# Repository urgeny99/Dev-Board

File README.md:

# This is a self made dev board that i can use on many different projects. For example mount it on a bread board and connect a small screen or something like that.
# Story
I made started this project without knowing almost anything about PCBs but with the time as i followed the tutrial more and more things got clear. I was not sure what to use this for but i started watching videos and and did research. It is actually a very cool project. I am not sure if it will be easy soldering at home but i like a challange so i'll try it.
I will probably be using this dev board with bread boards to try experimenting and i maybe order some more cool components to try out how they work. (e.g OLED screens, small sensors etc.)
## Parts
What this board has are:
- USB-C conmector
- 16Mb flash storage
- RP2040 "CPU"
- 12MHz Crystal Osillator
- Temperature sensor
- Small NeoPixel
- 20+ GPIO pins

## Based on @KaiTheJollyGuy’s tutorial on how to make a devboard

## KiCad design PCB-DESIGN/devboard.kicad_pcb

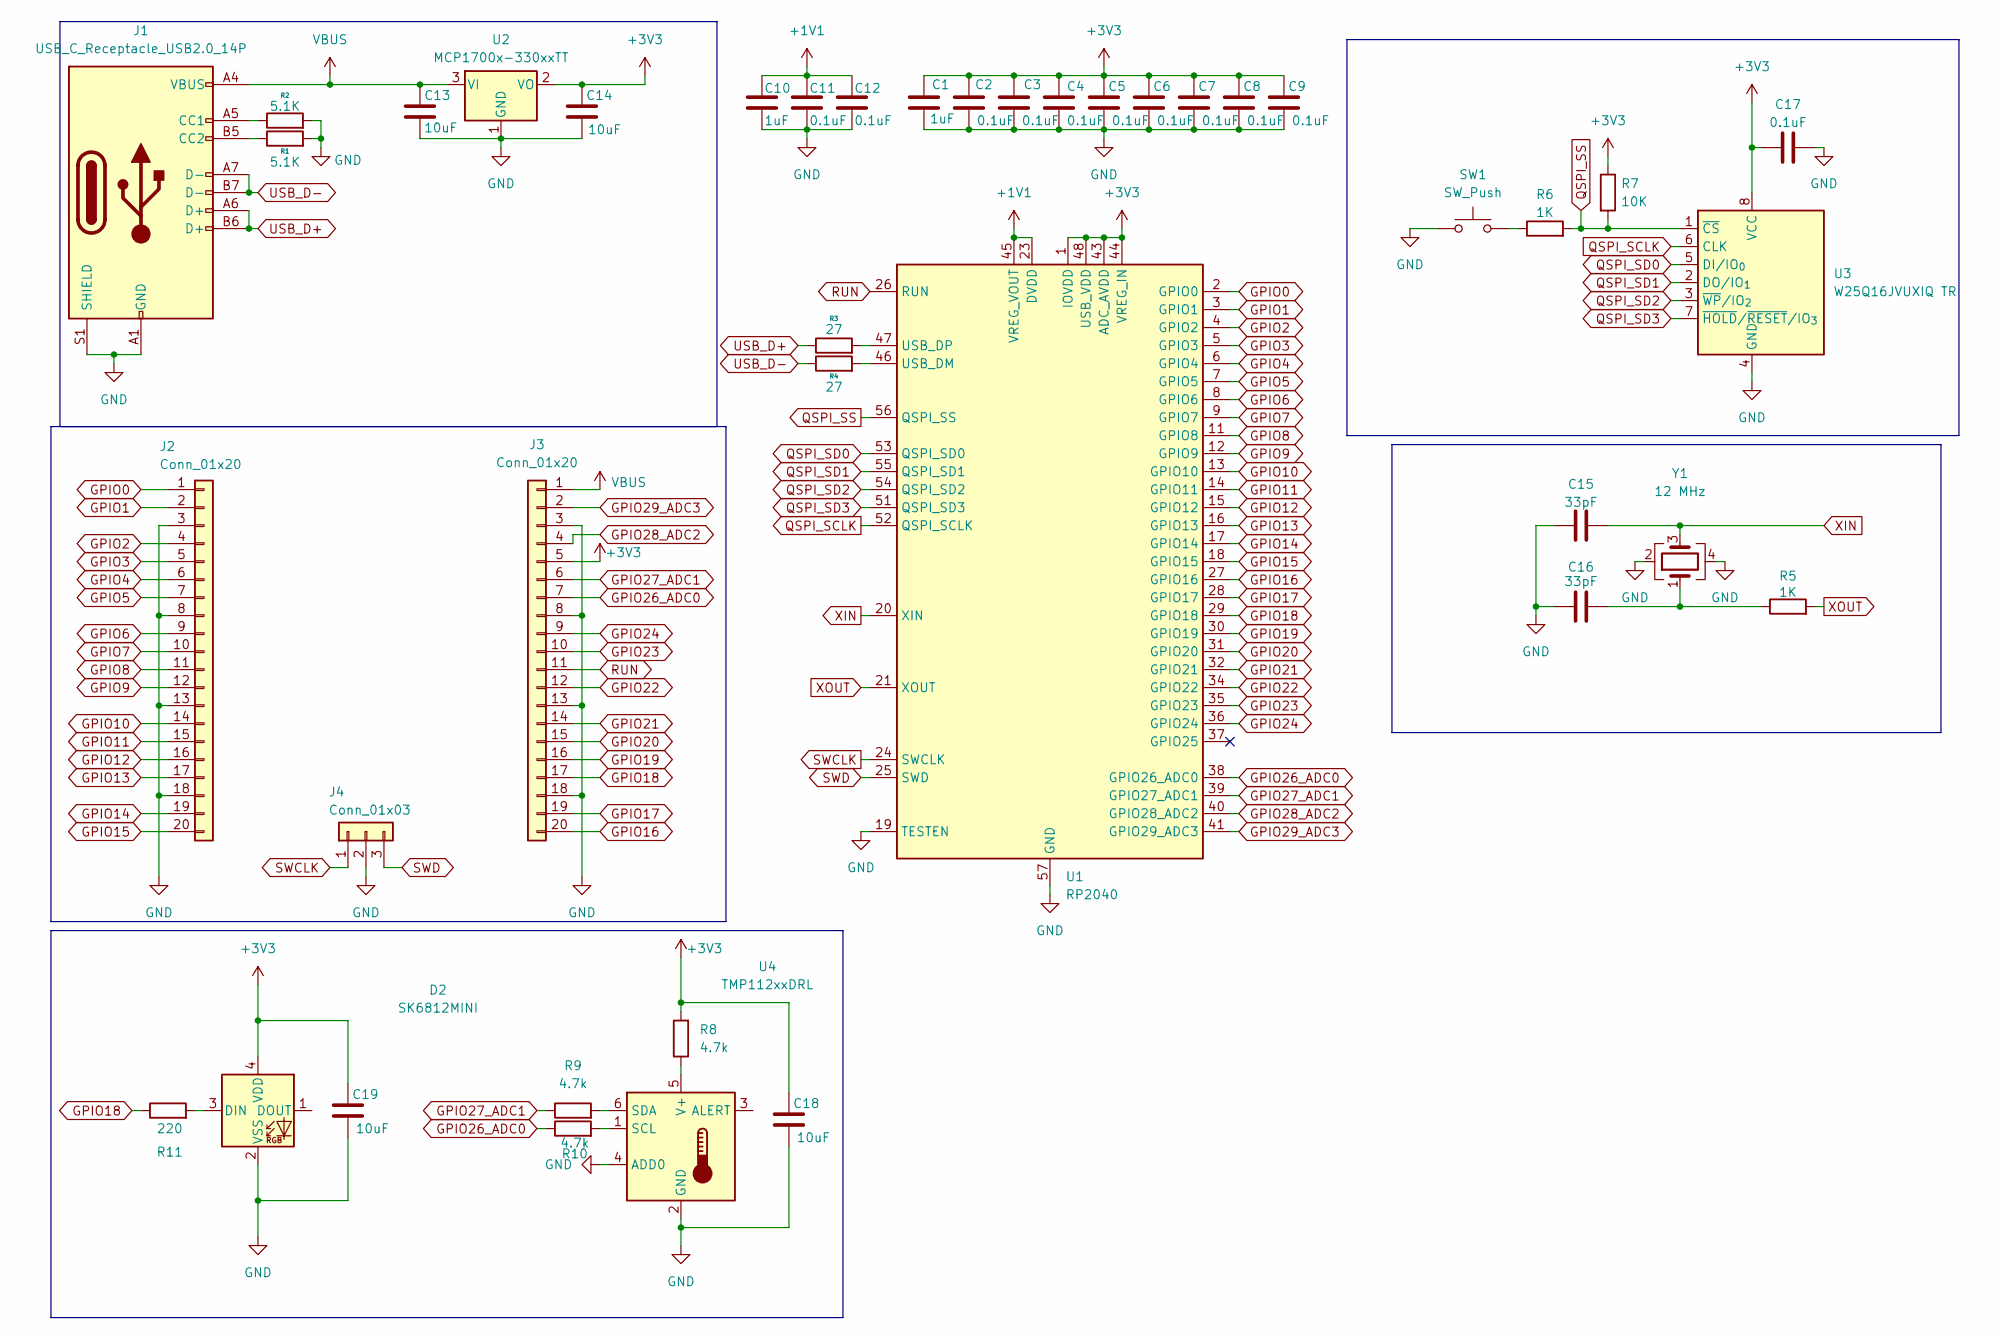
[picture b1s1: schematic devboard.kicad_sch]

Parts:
C1, C10: 1uF; C_0603_1608Metric
C2, C3, C4, C5, C6, C7, C8, C9, C11, C12, C17: 0.1uF; C_0603_1608Metric
C13, C14: 10uF; C_0805_2012Metric
C15, C16: 33pF; C_0603_1608Metric
C18, C19: 10uF; C_0603_1608Metric
D2: SK6812MINI; LED_SK6812MINI_PLCC4_3.5x3.5mm_P1.75mm
J1: USB_C_Receptacle_USB2.0_14P; USB_C_Receptacle_HRO_TYPE-C-31-M-12
J2, J3: Conn_01x20; PinHeader_1x20_P2.54mm_Vertical
J4: Conn_01x03; PinHeader_1x03_P2.54mm_Vertical
R1, R2: 5.1K; R_0603_1608Metric
R3, R4: 27; R_0603_1608Metric
R5, R6: 1K; R_0603_1608Metric
R7: 10K; R_0603_1608Metric
R8, R9, R10: 4.7k; R_0603_1608Metric
R11: 220; R_0603_1608Metric
SW1: SW_Push; SW_Push_SPST_NO_Alps_SKRK
U1: RP2040; QFN-56-1EP_7x7mm_P0.4mm_EP3.2x3.2mm
U2: MCP1700x-330xxTT; SOT-23
U3: W25Q16JVUXIQ TR; Winbond_USON-8-1EP_3x2mm_P0.5mm_EP0.2x1.6mm
U4: TMP112xxDRL; SOT-563
Y1: 12 MHz; Crystal_SMD_3225-4Pin_3.2x2.5mm

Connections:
+1V1: C10.1, C11.1, C12.1, U1.23 (DVDD), U1.45 (VREG_VOUT), U1.50 (DVDD)
+3V3: C1.1, C2.1, C3.1, C4.1, C5.1, C6.1, C7.1, C8.1, C9.1, C14.1, C17.1, C18.1, C19.1, D2.4 (VDD), J3.5, R7.1, R8.2, U1.1 (IOVDD), U1.10 (IOVDD), U1.22 (IOVDD), U1.33 (IOVDD), U1.42 (IOVDD), U1.43 (ADC_AVDD), U1.44 (VREG_IN), U1.48 (USB_VDD), U1.49 (IOVDD), U2.2 (VO), U3.8 (VCC)
GND: C1.2, C2.2, C3.2, C4.2, C5.2, C6.2, C7.2, C8.2, C9.2, C10.2, C11.2, C12.2, C13.2, C14.2, C15.1, C16.1, C17.2, C18.2, C19.2, D2.2 (VSS), J1.A1 (GND), J1.A12 (GND), J1.B1 (GND), J1.B12 (GND), J1.S1 (SHIELD), J2.3, J2.8, J2.13, J2.18, J3.3, J3.8, J3.13, J3.18, J4.2, R1.2, R2.2, SW1.1, U1.19 (TESTEN), U1.57 (GND), U2.1 (GND), U3.4 (GND), U4.2 (GND), U4.4 (ADD0), Y1.2, Y1.4
GPIO0: J2.1, U1.2 (GPIO0)
GPIO1: J2.2, U1.3 (GPIO1)
GPIO2: J2.4, U1.4 (GPIO2)
GPIO3: J2.5, U1.5 (GPIO3)
GPIO4: J2.6, U1.6 (GPIO4)
GPIO5: J2.7, U1.7 (GPIO5)
GPIO6: J2.9, U1.8 (GPIO6)
GPIO7: J2.10, U1.9 (GPIO7)
GPIO8: J2.11, U1.11 (GPIO8)
GPIO9: J2.12, U1.12 (GPIO9)
GPIO10: J2.14, U1.13 (GPIO10)
GPIO11: J2.15, U1.14 (GPIO11)
GPIO12: J2.16, U1.15 (GPIO12)
GPIO13: J2.17, U1.16 (GPIO13)
GPIO14: J2.19, U1.17 (GPIO14)
GPIO15: J2.20, U1.18 (GPIO15)
GPIO16: J3.20, U1.27 (GPIO16)
GPIO17: J3.19, U1.28 (GPIO17)
GPIO18: J3.17, R11.1, U1.29 (GPIO18)
GPIO19: J3.16, U1.30 (GPIO19)
GPIO20: J3.15, U1.31 (GPIO20)
GPIO21: J3.14, U1.32 (GPIO21)
GPIO22: J3.12, U1.34 (GPIO22)
GPIO23: J3.10, U1.35 (GPIO23)
GPIO24: J3.9, U1.36 (GPIO24)
GPIO26_ADC0: J3.7, R10.1, U1.38 (GPIO26_ADC0)
GPIO27_ADC1: J3.6, R9.1, U1.39 (GPIO27_ADC1)
GPIO28_ADC2: J3.4, U1.40 (GPIO28_ADC2)
GPIO29_ADC3: J3.2, U1.41 (GPIO29_ADC3)
unnamed: C16.2, R5.1, Y1.1
unnamed: D2.3 (DIN), R11.2
unnamed: J1.A5 (CC1), R2.1
unnamed: J1.B5 (CC2), R1.1
unnamed: R6.1, SW1.2
unnamed: R4.2, U1.46 (USB_DM)
unnamed: R3.2, U1.47 (USB_DP)
unnamed: R10.2, U4.1 (SCL)
unnamed: R9.2, U4.6 (SDA)
unnamed: R8.1, U4.5 (V+)
QSPI_SCLK: U1.52 (QSPI_SCLK), U3.6 (CLK)
QSPI_SD0: U1.53 (QSPI_SD0), U3.5 (DI/IO_{0})
QSPI_SD1: U1.55 (QSPI_SD1), U3.2 (DO/IO_{1})
QSPI_SD2: U1.54 (QSPI_SD2), U3.3 (~WP/IO_{2})
QSPI_SD3: U1.51 (QSPI_SD3), U3.7 (~HOLD/~RESET/IO_{3})
QSPI_SS: R6.2, R7.2, U1.56 (QSPI_SS), U3.1 (~CS)
RUN: J3.11, U1.26 (RUN)
SWCLK: J4.1, U1.24 (SWCLK)
SWD: J4.3, U1.25 (SWD)
USB_D+: J1.A6 (D+), J1.B6 (D+), R3.1
USB_D-: J1.A7 (D-), J1.B7 (D-), R4.1
VBUS: C13.1, J1.A4 (VBUS), J1.A9 (VBUS), J1.B4 (VBUS), J1.B9 (VBUS), J3.1, U2.3 (VI)
XIN: C15.2, U1.20 (XIN), Y1.3
XOUT: R5.2, U1.21 (XOUT)

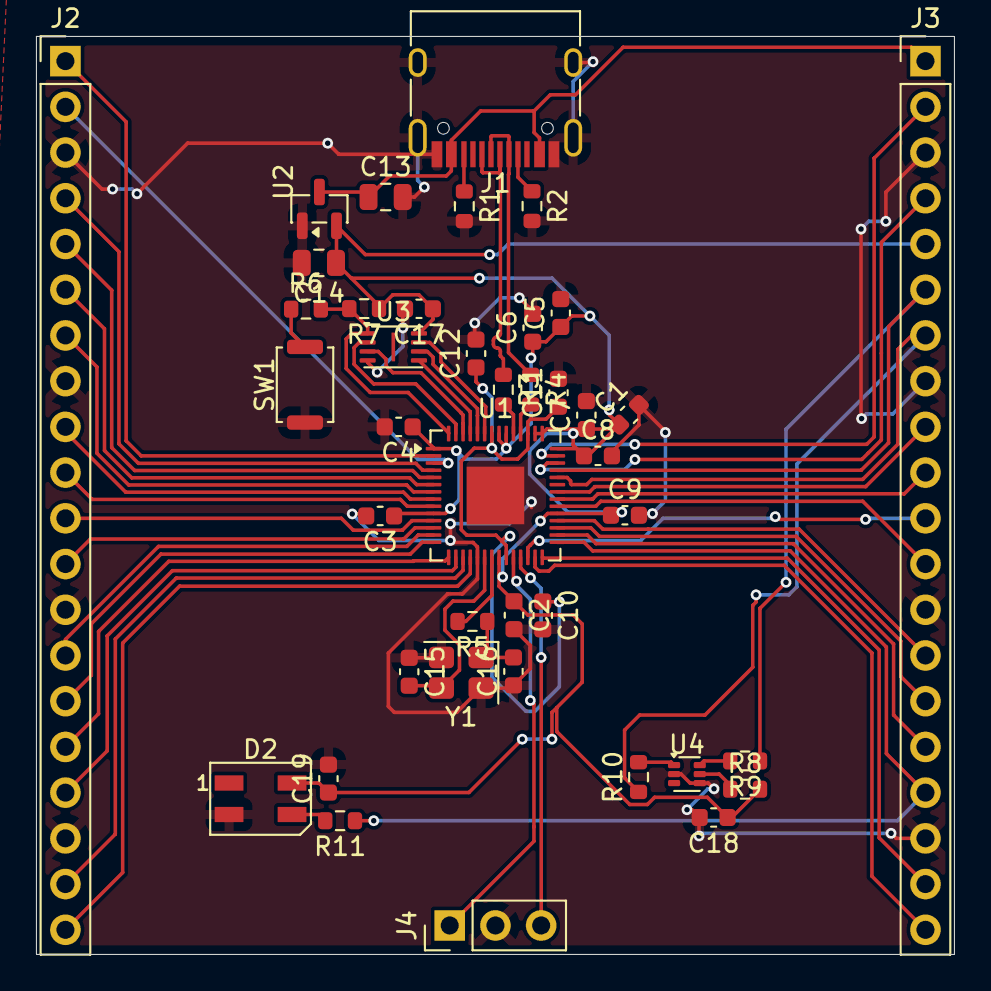
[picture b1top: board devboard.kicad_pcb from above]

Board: 2 copper layers, 51.0 x 51.0 mm, 41 parts (0 on the bottom side), 56 nets.

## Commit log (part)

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2026-01-13 Add header row and new product entries to BOM.csv
    The BOM.csv file was updated to include a new header row and additional product entries.
2026-01-13 Create Checkout cart LCSC
2026-01-13 Create
2026-01-13 Create a
2026-01-13 Rename
2026-01-13 Rena
